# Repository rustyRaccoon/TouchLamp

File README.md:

# TouchLamp
 Portable LED lamp with touch button on top

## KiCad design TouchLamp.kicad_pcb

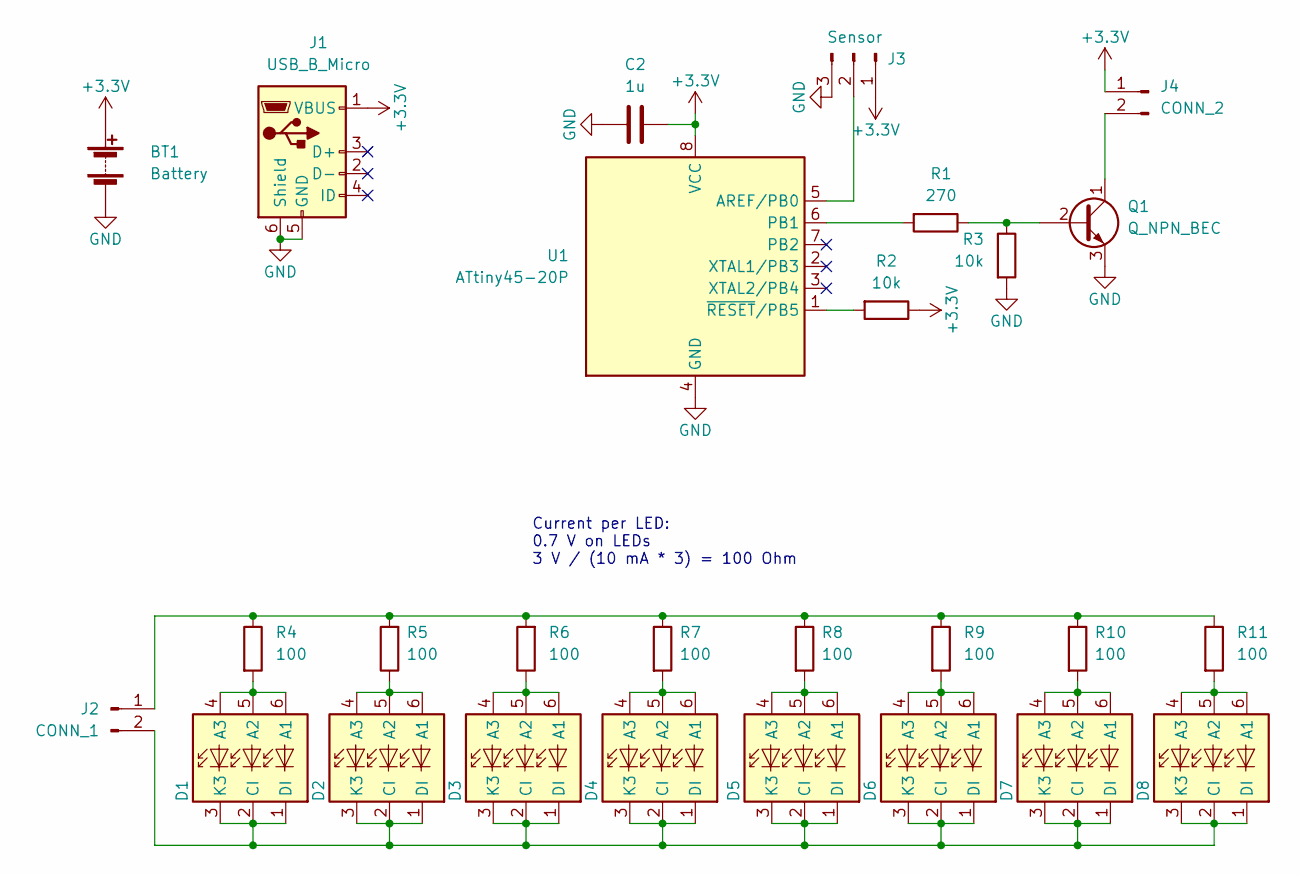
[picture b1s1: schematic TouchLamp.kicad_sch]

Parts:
BT1: Battery; PinHeader_1x02_P2.54mm_Vertical
C2: 1u; FakeSMD_C_Disc
D1, D2, D3, D4, D5, D6, D7, D8: 5050_led_(3-in-1); LED_RGB_5050-6
J1: USB_B_Micro; USB_Micro-B_Amphenol_10103594-0001LF_Horizontal
J2: CONN_1; PinHeader_1x02_P2.54mm_Vertical
J3: Sensor; PinHeader_1x03_P1.27mm_Vertical
J4: CONN_2; PinHeader_1x02_P1.27mm_Vertical
Q1: Q_NPN_BEC; FakeSMD_TO-92-3_Vertical
R1: 270; R_0805_2012Metric
R2, R3: 10k; R_0805_2012Metric
R4, R5, R6, R7, R8, R9, R10, R11: 100; R_0805_2012Metric
U1: ATtiny45-20P; FakeSMD_DIP-8

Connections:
+3V3: BT1.1 (+), C2.2, J1.1 (VBUS), J3.1, J4.1, R2.1, U1.8 (VCC)
GND: BT1.2 (-), C2.1, J1.5 (GND), J1.6 (Shield), J3.3, Q1.3 (E), R3.2, U1.4 (GND)
unnamed: D1.1 (DI), D1.2 (CI), D1.3 (K3), D2.1 (DI), D2.2 (CI), D2.3 (K3), D3.1 (DI), D3.2 (CI), D3.3 (K3), D4.1 (DI), D4.2 (CI), D4.3 (K3), D5.1 (DI), D5.2 (CI), D5.3 (K3), D6.1 (DI), D6.2 (CI), D6.3 (K3), D7.1 (DI), D7.2 (CI), D7.3 (K3), D8.1 (DI), D8.2 (CI), D8.3 (K3), J2.2
unnamed: D1.4 (A3), D1.5 (A2), D1.6 (A1), R4.2
unnamed: D2.4 (A3), D2.5 (A2), D2.6 (A1), R5.1
unnamed: D3.4 (A3), D3.5 (A2), D3.6 (A1), R6.1
unnamed: D4.4 (A3), D4.5 (A2), D4.6 (A1), R7.2
unnamed: D5.4 (A3), D5.5 (A2), D5.6 (A1), R8.2
unnamed: D6.4 (A3), D6.5 (A2), D6.6 (A1), R9.2
unnamed: D7.4 (A3), D7.5 (A2), D7.6 (A1), R10.2
unnamed: D8.4 (A3), D8.5 (A2), D8.6 (A1), R11.2
unnamed: J2.1, R4.1, R5.2, R6.2, R7.1, R8.1, R9.1, R10.1, R11.1
unnamed: J3.2, U1.5 (AREF/PB0)
unnamed: J4.2, Q1.1 (C)
unnamed: Q1.2 (B), R1.1, R3.1
unnamed: R1.2, U1.6 (PB1)
unnamed: R2.2, U1.1 (~RESET/PB5)

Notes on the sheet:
Current per LED: 0.7 V on LEDs 3 V / (10 mA * 3) = 100 Ohm

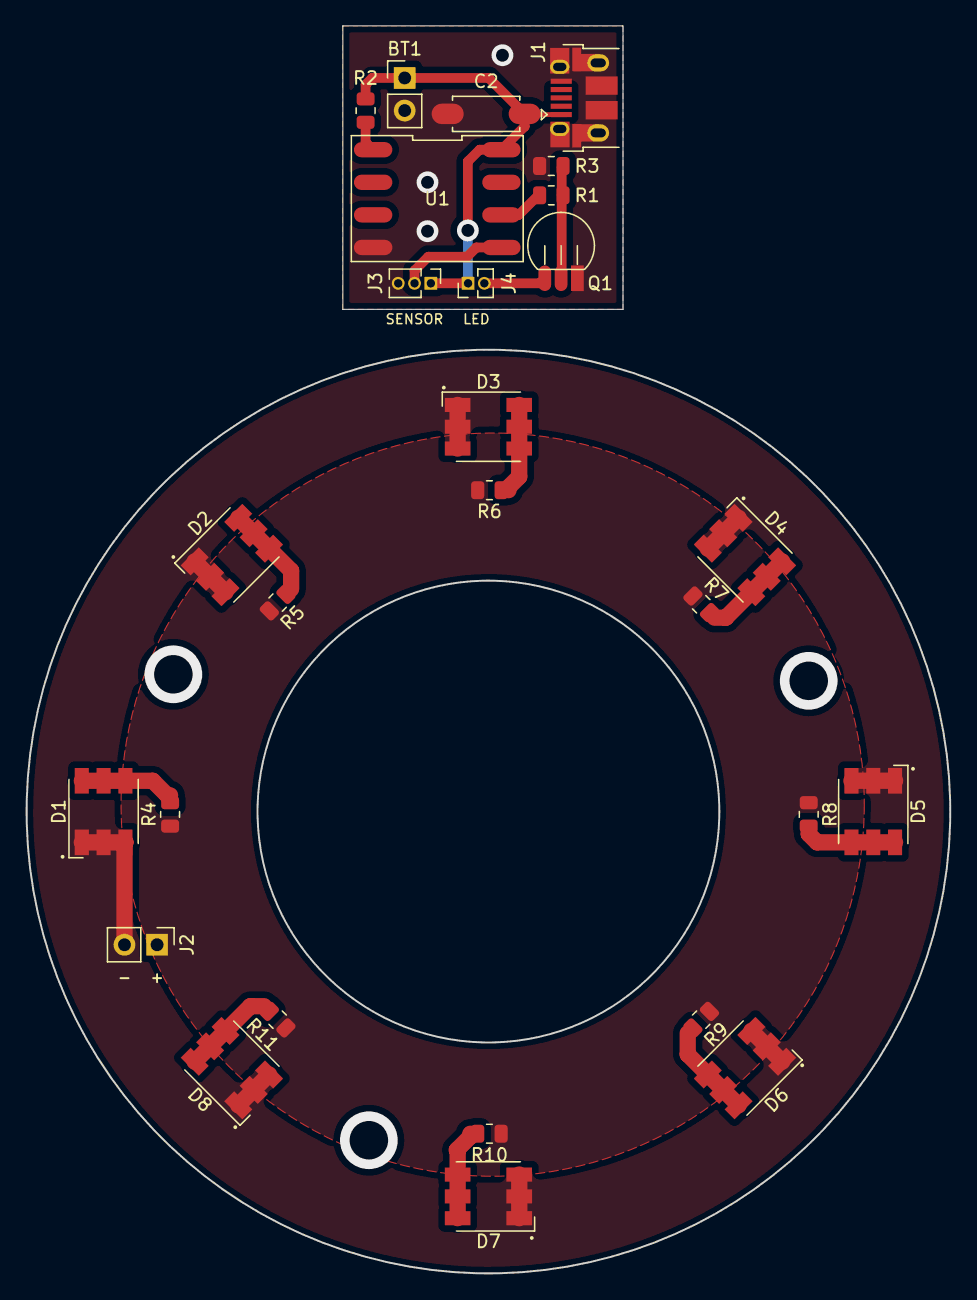
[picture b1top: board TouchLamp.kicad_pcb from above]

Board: 2 copper layers, 72.0 x 97.2 mm, 27 parts (0 on the bottom side), 17 nets.
